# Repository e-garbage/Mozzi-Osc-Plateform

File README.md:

# Mozzi Osc Plateform
### Eurorack ready Developement plateform for the arduino librairy Mozzi  

### Concept

Inpsired by Hagiwo's projects around arduino nano boards and Mozzi Librairy, I created this rather simple oscillator oriented developpement plateform.
This allow to connect quickly four knob, one 1V/oct input, and one Audio out (eurorack level) to your arduino nano board. This way, you can develop your dream oscillator (or any kind of sound module you want) super easily!!

### Interface board

/*wip*/

### Code

/*wip*/

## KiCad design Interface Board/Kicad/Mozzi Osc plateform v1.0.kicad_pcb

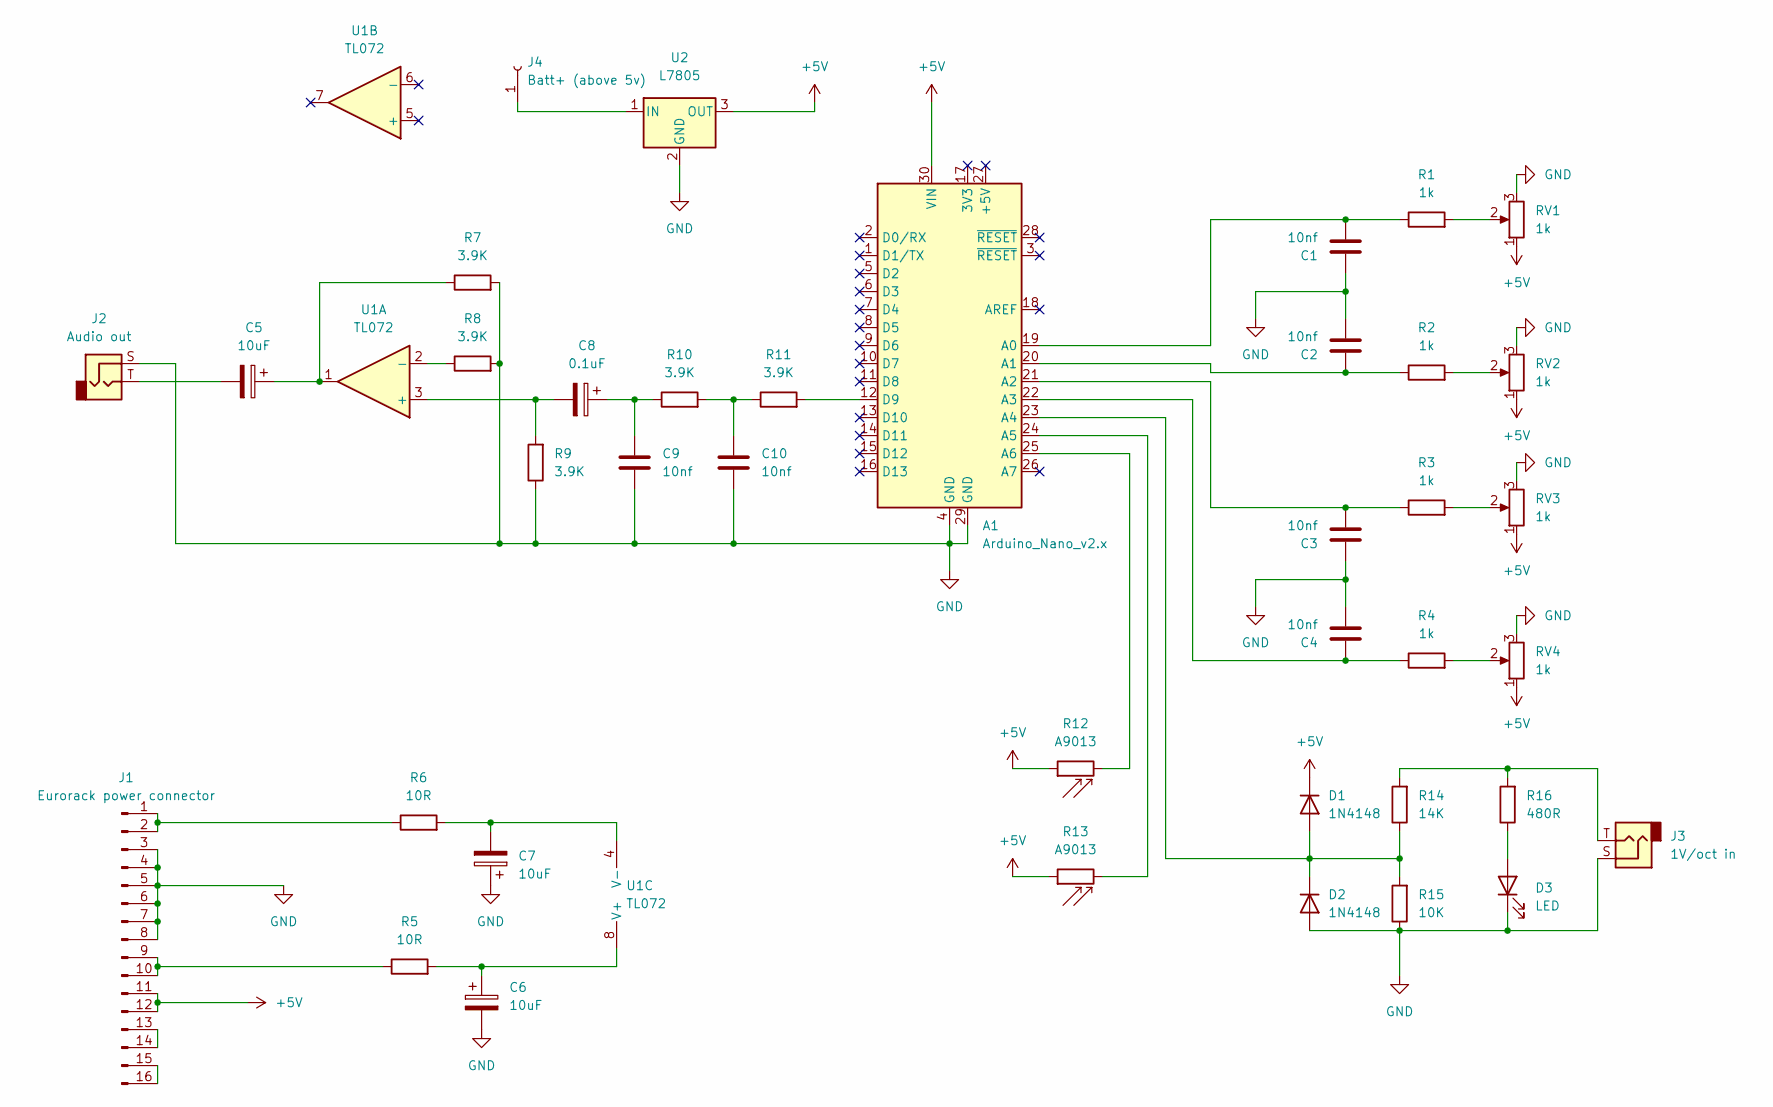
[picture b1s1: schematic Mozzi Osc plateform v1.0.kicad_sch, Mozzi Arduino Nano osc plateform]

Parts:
A1: Arduino_Nano_v2.x; Arduino_Nano
C1, C2, C3, C4, C9, C10: 10nf; C_Disc_D3.0mm_W1.6mm_P2.50mm
C5, C6, C7: 10uF; CP_Radial_D4.0mm_P2.00mm
C8: 0.1uF; CP_Radial_D4.0mm_P1.50mm
D1, D2: 1N4148; D_DO-35_SOD27_P7.62mm_Horizontal
D3: LED; LED_D5.0mm_Clear
J1: Eurorack power connector; PinHeader_2x08_P2.54mm_Vertical
J2: Audio out; PinHeader_1x02_P2.54mm_Vertical_Audio_out
J3: 1V/oct in; PinHeader_1x02_P2.54mm_Vertical_Audio_out
J4: Batt+ (above 5v); PinHeader_1x01_P2.54mm_Vertical
R1, R2, R3, R4: 1k; R_Axial_DIN0207_L6.3mm_D2.5mm_P7.62mm_Horizontal
R5, R6: 10R; R_Axial_DIN0207_L6.3mm_D2.5mm_P7.62mm_Horizontal
R7, R8, R9, R10, R11: 3.9K; R_Axial_DIN0207_L6.3mm_D2.5mm_P7.62mm_Horizontal
R12, R13: A9013; R_LDR_5.0x4.1mm_P3mm_Vertical
R14: 14K; R_Axial_DIN0207_L6.3mm_D2.5mm_P7.62mm_Horizontal
R15: 10K; R_Axial_DIN0207_L6.3mm_D2.5mm_P7.62mm_Horizontal
R16: 480R; R_Axial_DIN0207_L6.3mm_D2.5mm_P7.62mm_Horizontal
RV1, RV2, RV3, RV4: 1k; PinHeader_1x03_P2.54mm_Vertical
U1: TL072; DIP-8_W10.16mm
U2: L7805; TO-92

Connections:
+5V: A1.30 (VIN), D1.1 (K), J1.11, J1.12, R12.1, R13.1, RV1.1, RV2.1, RV3.1, RV4.1, U2.3 (OUT)
GND: A1.4 (GND), A1.29 (GND), C1.1, C2.2, C3.1, C4.2, C6.2, C7.1, C9.2, C10.2, D2.2 (A), D3.1 (K), J1.3, J1.4, J1.5, J1.6, J1.7, J1.8, J2.S, J3.S, R7.2, R8.2, R9.1, R15.1, RV1.3, RV2.3, RV3.3, RV4.3, U2.2 (GND); also elsewhere on the board
unnamed: A1.12 (D9), R11.2
unnamed: A1.19 (A0), C1.2, R1.1
unnamed: A1.20 (A1), C2.1, R2.1
unnamed: A1.21 (A2), C3.2, R3.1
unnamed: A1.22 (A3), C4.1, R4.1
unnamed: A1.23 (A4), D1.2 (A), D2.1 (K), R14.1, R15.2
unnamed: A1.24 (A5), R13.2
unnamed: A1.25 (A6), R12.2
unnamed: C5.1, R7.1, U1.1
unnamed 11: C5.2, J2.T; also elsewhere on the board
unnamed: C6.1, R5.2, U1.8 (V+)
unnamed: C7.2, R6.2, U1.4 (V-)
unnamed: C8.1, C9.1, R10.1
unnamed: C8.2, R9.2, U1.3 (+)
unnamed: C10.1, R10.2, R11.1
unnamed: D3.2 (A), R16.1
unnamed: J1.1, J1.2, R6.1
unnamed: J1.9, J1.10, R5.1
unnamed: J1.13, J1.14
unnamed: J1.15, J1.16
unnamed 22: J3.T, R14.2, R16.2; also elsewhere on the board
unnamed: R1.2, RV1.2
unnamed: R2.2, RV2.2
unnamed: R3.2, RV3.2
unnamed: R4.2, RV4.2
unnamed: R8.1, U1.2 (-)
unnamed: J4.1, U2.1 (IN)

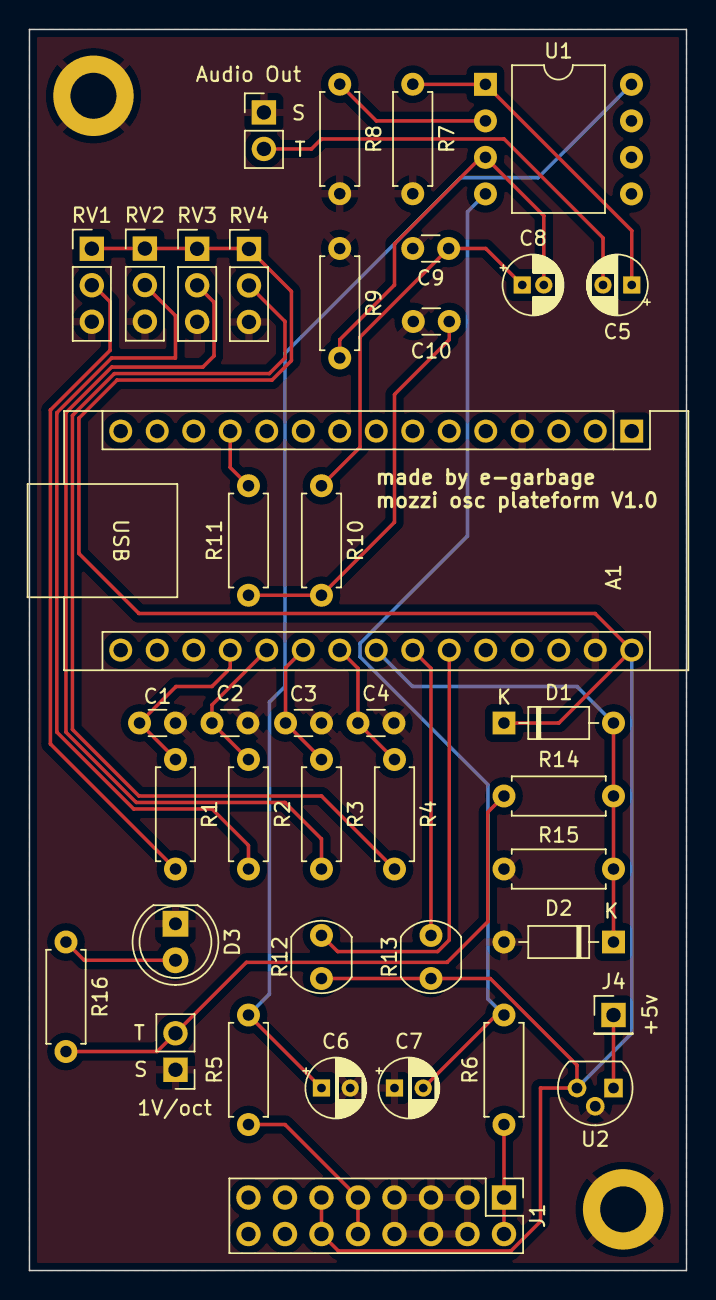
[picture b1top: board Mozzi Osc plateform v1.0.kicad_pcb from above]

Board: 2 copper layers, 45.7 x 86.4 mm, 40 parts (0 on the bottom side), 29 nets.

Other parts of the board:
1V/oct: 1V/oct in; PinHeader_1x02_P2.54mm_Vertical_Audio_out
Audio Out: Audio out; PinHeader_1x02_P2.54mm_Vertical_Audio_out

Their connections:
GND: 1V/oct.S, Audio Out.S; also elsewhere on the board
unnamed 11: Audio Out.T; also elsewhere on the board
unnamed 22: 1V/oct.T; also elsewhere on the board

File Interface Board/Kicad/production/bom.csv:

Designator,Footprint,Quantity,Value,LCSC Part #
1V/oct,PinHeader_1x02_P2.54mm_Vertical_Audio_out,1,1V/oct in,
A1,Arduino_Nano,1,Arduino_Nano_v2.x,
Audio Out,PinHeader_1x02_P2.54mm_Vertical_Audio_out,1,Audio out,
"C1, C10, C2, C3, C4, C9",C_Disc_D3.0mm_W1.6mm_P2.50mm,6,10nf,
"C5, C6, C7",CP_Radial_D4.0mm_P2.00mm,3,10uF,
C8,CP_Radial_D4.0mm_P1.50mm,1,0.1uF,
"D1, D2",D_DO-35_SOD27_P7.62mm_Horizontal,2,1N4148,
D3,LED_D5.0mm_Clear,1,LED,
J1,PinHeader_2x08_P2.54mm_Vertical,1,Eurorack power connector,
J4,PinHeader_1x01_P2.54mm_Vertical,1,Batt+ (above 5v),
"R1, R2, R3, R4",R_Axial_DIN0207_L6.3mm_D2.5mm_P7.62mm_Horizontal,4,1k,
"R10, R11, R7, R8, R9",R_Axial_DIN0207_L6.3mm_D2.5mm_P7.62mm_Horizontal,5,3.9K,
"R12, R13",R_LDR_5.0x4.1mm_P3mm_Vertical,2,A9013,
R14,R_Axial_DIN0207_L6.3mm_D2.5mm_P7.62mm_Horizontal,1,14K,
R15,R_Axial_DIN0207_L6.3mm_D2.5mm_P7.62mm_Horizontal,1,10K,
R16,R_Axial_DIN0207_L6.3mm_D2.5mm_P7.62mm_Horizontal,1,480R,
"R5, R6",R_Axial_DIN0207_L6.3mm_D2.5mm_P7.62mm_Horizontal,2,10R,
"RV1, RV2, RV3, RV4",PinHeader_1x03_P2.54mm_Vertical,4,1k,
U1,DIP-8_W10.16mm,1,TL072,
U2,TO-92,1,L7805,

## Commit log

2023-04-10 file structure, readme, Pcb and schemetics files
